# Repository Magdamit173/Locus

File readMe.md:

LOCUS: A LOCAL OFF-GRID COMMUNICATION NETWORK FOR UNINTERRUPTED SAFETY USING ESP32 AND ESP-NOW MESH TOPOLOGY IN THE UNIVERSITY OF CALOOCAN CITY COLLEGE OF ENGINEERING BUILDING

credits:

- https://github.com/jahm86/esp-32-kicad-library

- https://grabcad.com/library/tp5000-module-1
- https://grabcad.com/library/mt3608-boost-converter-dc-dc-module-1
- https://grabcad.com/library/battery-32650-with-screw-terminals-1

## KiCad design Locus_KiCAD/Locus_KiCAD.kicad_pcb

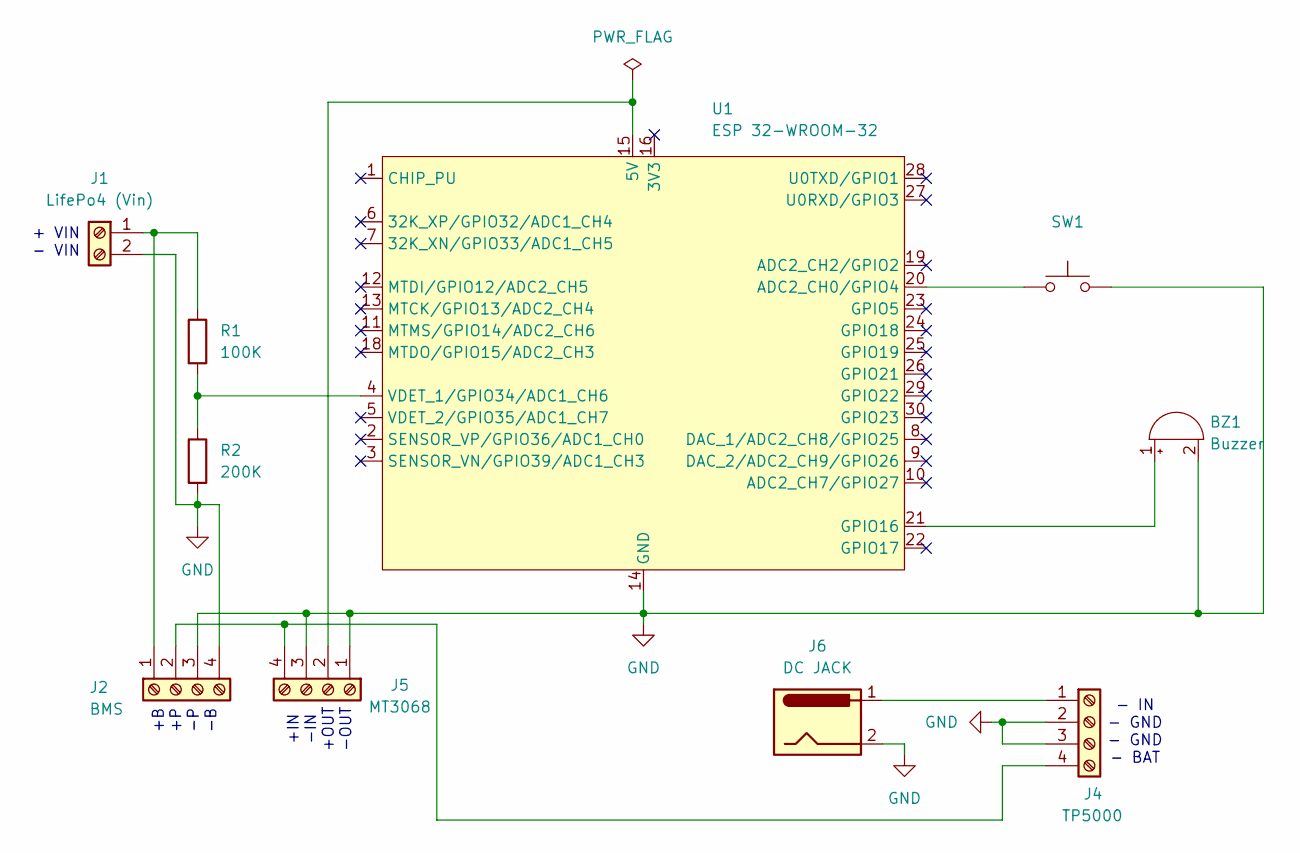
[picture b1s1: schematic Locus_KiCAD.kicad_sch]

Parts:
BZ1: Buzzer; TerminalBlock_Phoenix_MKDS-1,5-2_1x02_P5.00mm_Horizontal
J1: LifePo4 (Vin); TerminalBlock_Phoenix_MKDS-1,5-2_1x02_P5.00mm_Horizontal
J2: BMS; TerminalBlock_Phoenix_MKDS-1,5-4_1x04_P5.00mm_Horizontal
J4: TP5000; TerminalBlock_Phoenix_MKDS-1,5-4_1x04_P5.00mm_Horizontal
J5: MT3068; TerminalBlock_Phoenix_MKDS-1,5-4_1x04_P5.00mm_Horizontal
J6: DC JACK; TerminalBlock_Phoenix_MKDS-1,5-2_1x02_P5.00mm_Horizontal
R1: 100K; R_Axial_DIN0207_L6.3mm_D2.5mm_P10.16mm_Horizontal
R2: 200K; R_Axial_DIN0207_L6.3mm_D2.5mm_P10.16mm_Horizontal
SW1: EMERGENCY BUTTON; TerminalBlock_Phoenix_MKDS-1,5-2_1x02_P5.00mm_Horizontal
U1: ESP 32-WROOM-32; ESP32-DevKit-USB-C

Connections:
GND: BZ1.2 (-), J1.2, J2.3, J2.4, J4.2, J4.3, J5.1, J5.3, J6.2, R2.2, SW1.2, U1.14 (GND), U1.17 (GND)
unnamed: BZ1.1 (+), U1.21 (GPIO16)
unnamed: J1.1, J2.1, R1.1
unnamed: J2.2, J4.4, J5.4
unnamed: J4.1, J6.1
unnamed: J5.2, U1.15 (5V)
unnamed: SW1.1, U1.20 (ADC2_CH0/GPIO4)
unnamed: R1.2, R2.1, U1.4 (VDET_1/GPIO34/ADC1_CH6)

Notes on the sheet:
+B +P -P -B
+IN -IN +OUT -OUT
- IN - GND - GND - BAT
+ VIN - VIN

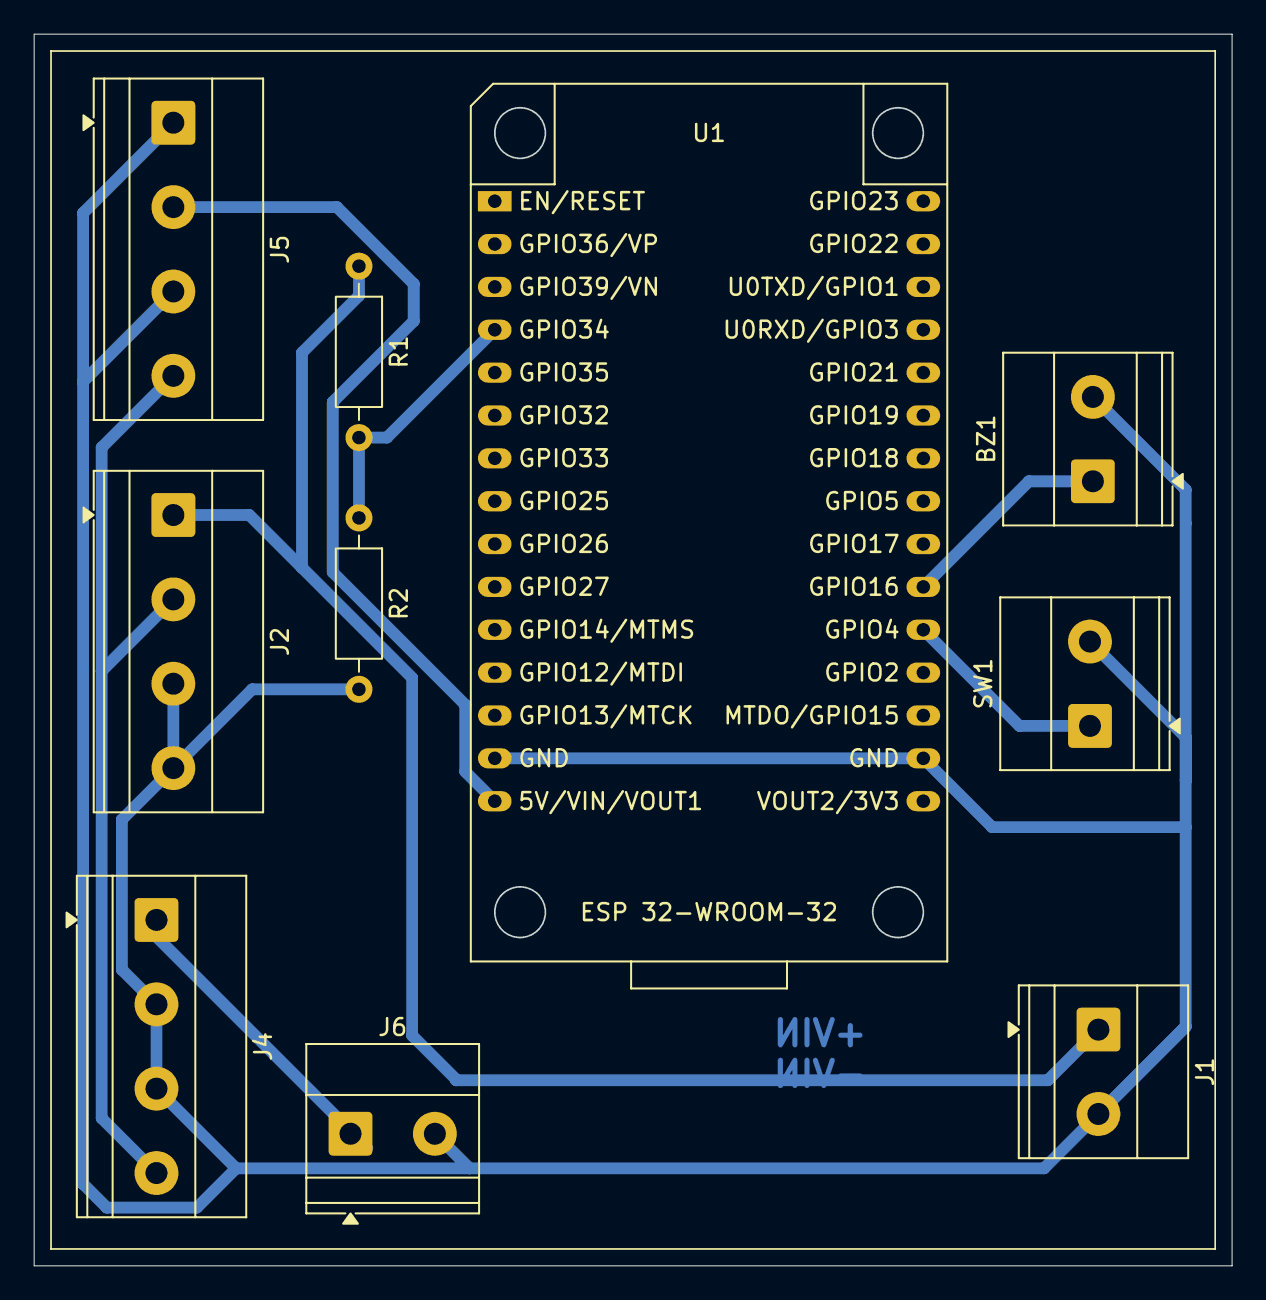
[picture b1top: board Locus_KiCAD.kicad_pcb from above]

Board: 2 copper layers, 71.0 x 73.0 mm, 10 parts (0 on the bottom side), 8 nets.

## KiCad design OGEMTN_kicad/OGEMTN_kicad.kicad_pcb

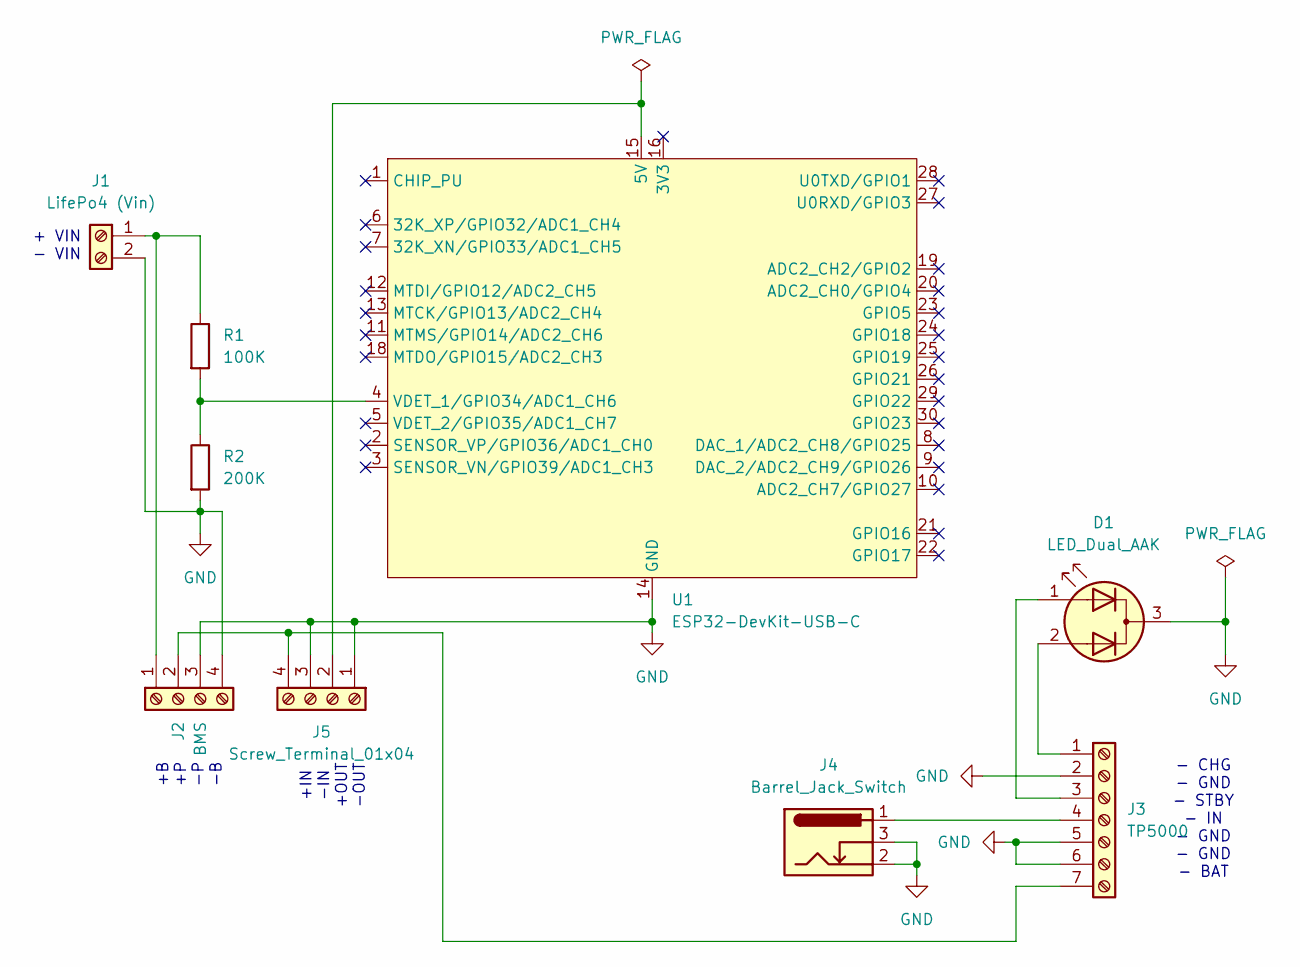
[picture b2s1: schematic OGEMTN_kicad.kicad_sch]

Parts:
D1: LED_Dual_AAK; LED_D3.0mm-3
J1: LifePo4 (Vin); TerminalBlock_Phoenix_MKDS-1,5-2_1x02_P5.00mm_Horizontal
J2: BMS; TerminalBlock_Phoenix_MKDS-1,5-4_1x04_P5.00mm_Horizontal
J3: TP5000; TerminalBlock_Phoenix_MKDS-1,5-7_1x07_P5.00mm_Horizontal
J4: Barrel_Jack_Switch; BarrelJack_GCT_DCJ200-10-A_Horizontal
J5: Screw_Terminal_01x04; TerminalBlock_Phoenix_MKDS-1,5-4_1x04_P5.00mm_Horizontal
R1: 100K; R_Axial_DIN0207_L6.3mm_D2.5mm_P10.16mm_Horizontal
R2: 200K; R_Axial_DIN0207_L6.3mm_D2.5mm_P10.16mm_Horizontal
U1: ESP32-DevKit-USB-C

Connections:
GND: D1.3 (K), J1.2, J2.3, J2.4, J3.2, J3.5, J3.6, J4.2, J4.3, J5.1, J5.3, R2.2, U1.14 (GND), U1.17 (GND)
unnamed: D1.1 (A1), J3.3
unnamed: D1.2 (A2), J3.1
unnamed: J1.1, J2.1, R1.1
unnamed: J2.2, J3.7, J5.4
unnamed: J3.4, J4.1
unnamed: J5.2, U1.15 (5V)
unnamed: R1.2, R2.1, U1.4 (VDET_1/GPIO34/ADC1_CH6)

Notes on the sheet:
+B +P -P -B
+IN -IN +OUT -OUT
- CHG - GND - STBY - IN - GND - GND - BAT
+ VIN - VIN

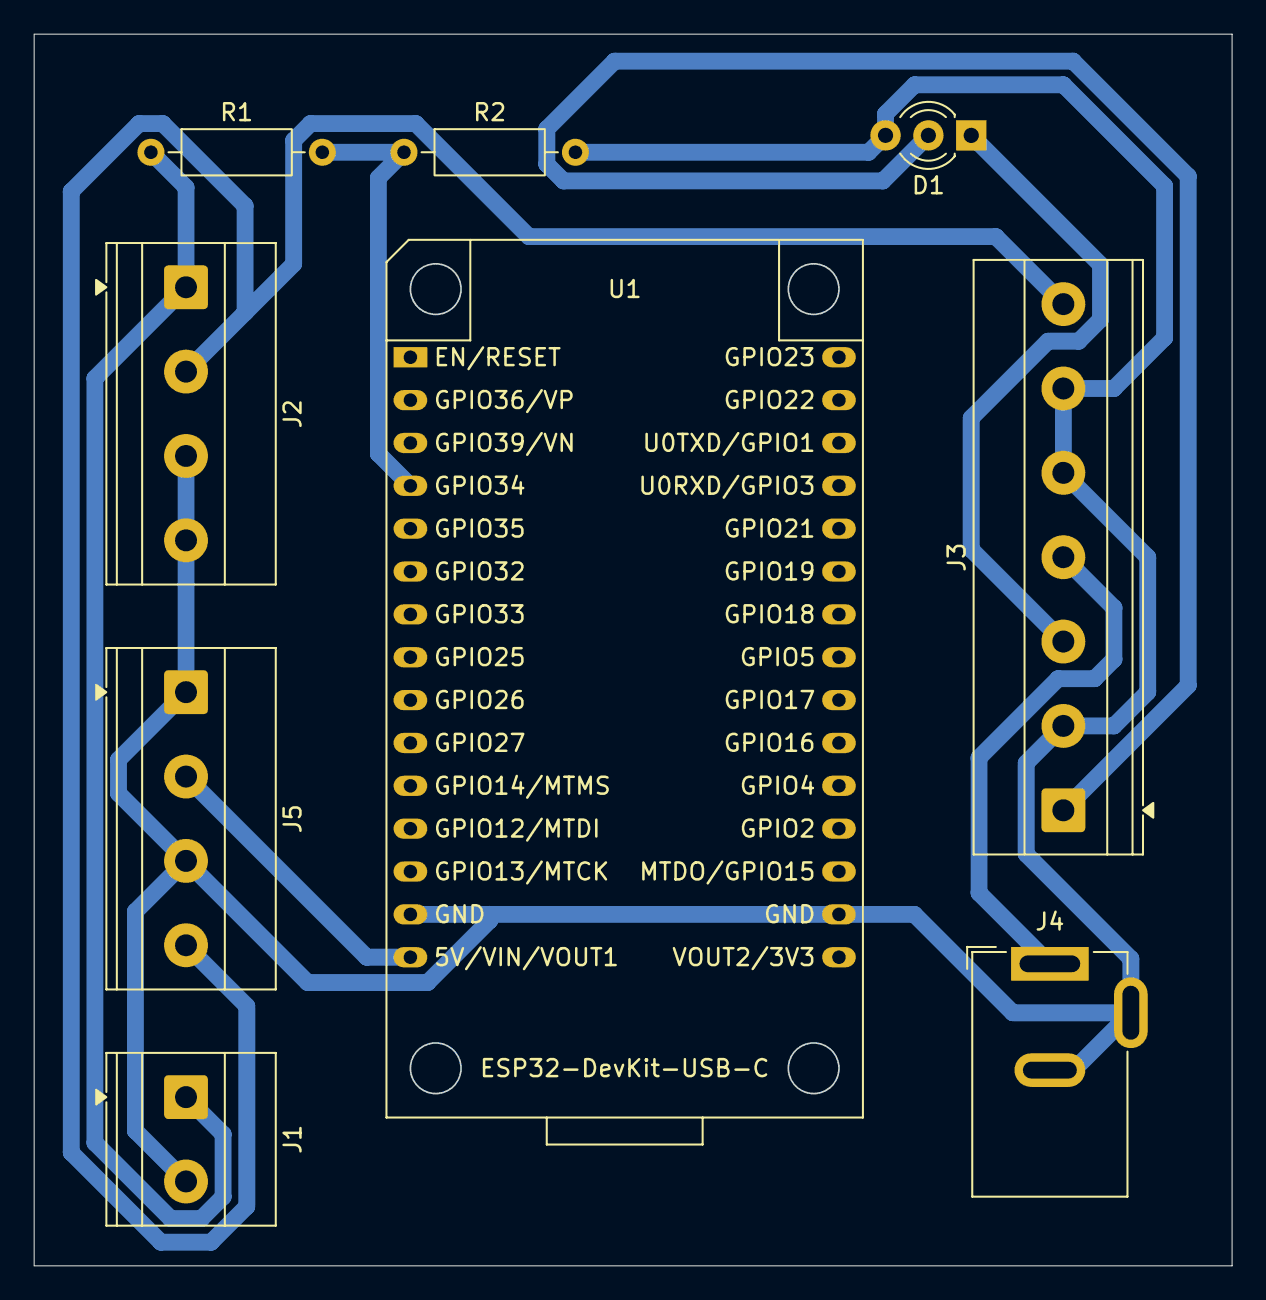
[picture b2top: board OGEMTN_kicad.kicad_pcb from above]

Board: 2 copper layers, 71.0 x 73.0 mm, 9 parts (0 on the bottom side), 8 nets.
